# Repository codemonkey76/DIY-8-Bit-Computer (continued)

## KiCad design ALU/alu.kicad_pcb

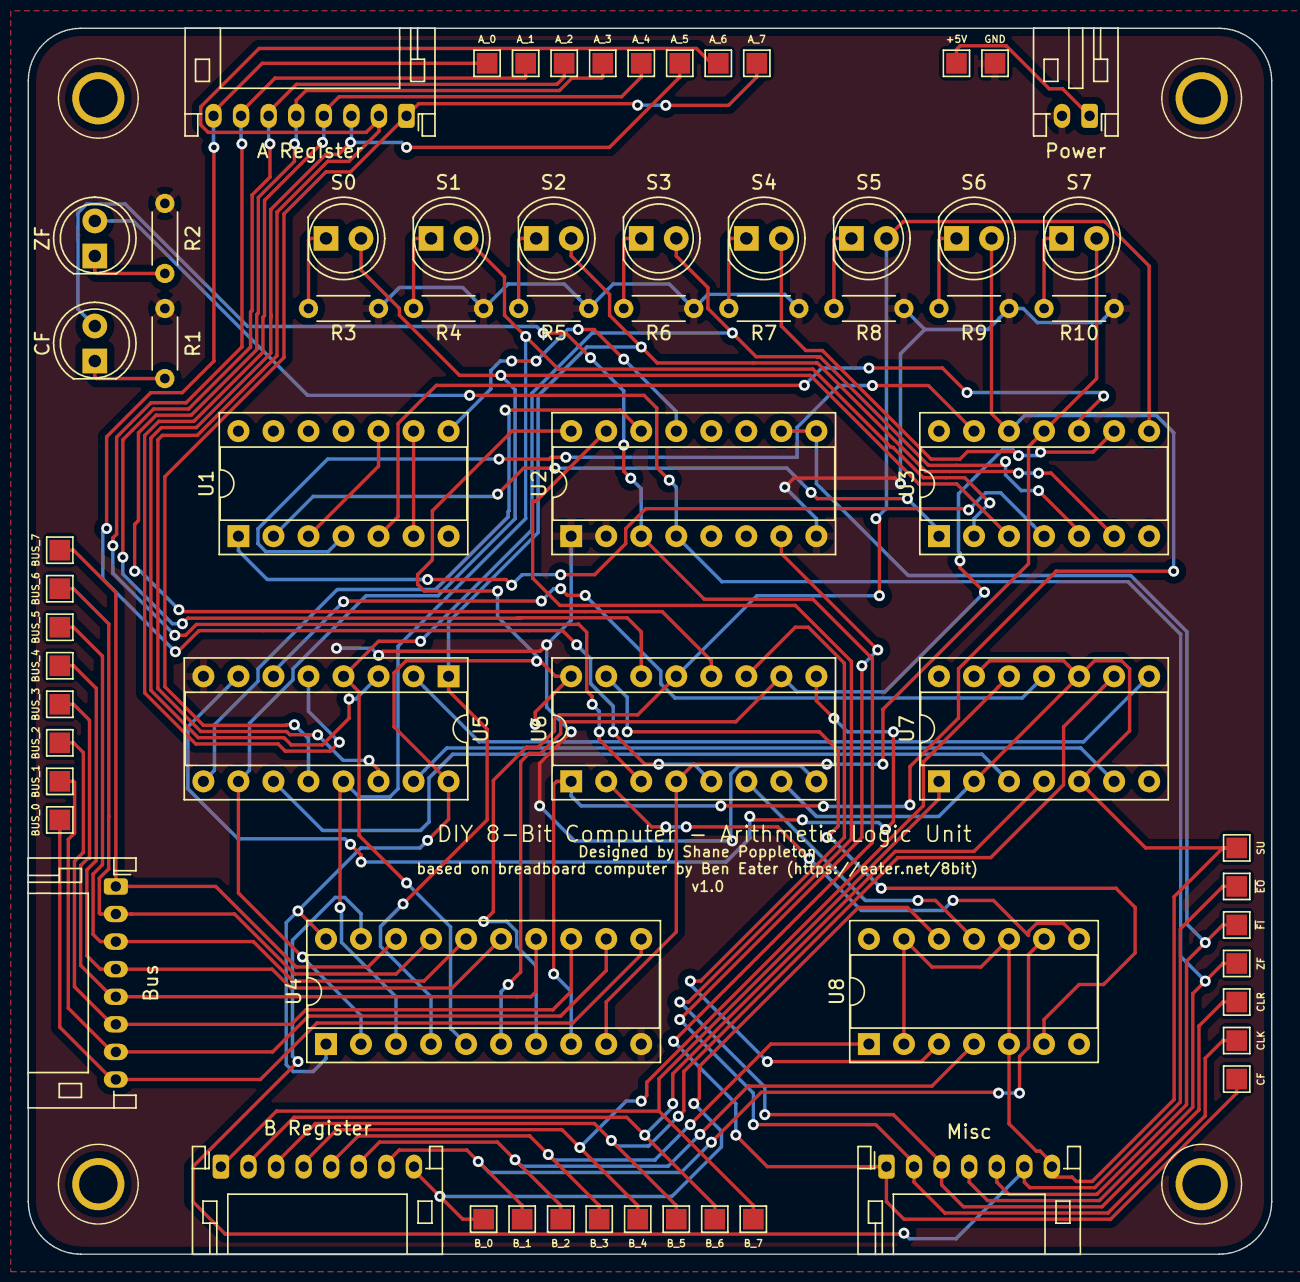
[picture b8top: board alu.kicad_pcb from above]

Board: 2 copper layers, 90.2 x 88.9 mm, 66 parts (0 on the bottom side), 68 nets.

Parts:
D1: CF; LED_D5.0mm
D2: ZF; LED_D5.0mm
D3: S0; LED_D5.0mm
D4: S1; LED_D5.0mm
D5: S2; LED_D5.0mm
D6: S3; LED_D5.0mm
D7: S4; LED_D5.0mm
D8: S5; LED_D5.0mm
D9: S6; LED_D5.0mm
D10: S7; LED_D5.0mm
J1: Bus; JST_PH_S8B-PH-K_1x08_P2.00mm_Horizontal
J2: Power; JST_PH_S2B-PH-K_1x02_P2.00mm_Horizontal
J3: Misc; JST_PH_S7B-PH-K_1x07_P2.00mm_Horizontal
J4: A Register; JST_PH_S8B-PH-K_1x08_P2.00mm_Horizontal
J5: B Register; JST_PH_S8B-PH-K_1x08_P2.00mm_Horizontal
R1, R2, R3, R4, R5, R6, R7, R8, R9, R10: 220R; R_Axial_DIN0204_L3.6mm_D1.6mm_P5.08mm_Horizontal
TP1: CF; TestPoint_Pad_1.5x1.5mm
TP2: ZF; TestPoint_Pad_1.5x1.5mm
TP3: ~FI~; TestPoint_Pad_1.5x1.5mm
TP4: CLK; TestPoint_Pad_1.5x1.5mm
TP5: CLR; TestPoint_Pad_1.5x1.5mm
TP6: BUS_0; TestPoint_Pad_1.5x1.5mm
TP7: BUS_1; TestPoint_Pad_1.5x1.5mm
TP8: BUS_2; TestPoint_Pad_1.5x1.5mm
TP9: BUS_3; TestPoint_Pad_1.5x1.5mm
TP10: BUS_4; TestPoint_Pad_1.5x1.5mm
TP11: BUS_5; TestPoint_Pad_1.5x1.5mm
TP12: BUS_6; TestPoint_Pad_1.5x1.5mm
TP13: BUS_7; TestPoint_Pad_1.5x1.5mm
TP14: +5V; TestPoint_Pad_1.5x1.5mm
TP15: GND; TestPoint_Pad_1.5x1.5mm
TP16: A_0; TestPoint_Pad_1.5x1.5mm
TP17: A_1; TestPoint_Pad_1.5x1.5mm
TP18: A_2; TestPoint_Pad_1.5x1.5mm
TP19: B_0; TestPoint_Pad_1.5x1.5mm
TP20: A_3; TestPoint_Pad_1.5x1.5mm
TP21: B_1; TestPoint_Pad_1.5x1.5mm
TP22: A_4; TestPoint_Pad_1.5x1.5mm
TP23: B_2; TestPoint_Pad_1.5x1.5mm
TP24: A_5; TestPoint_Pad_1.5x1.5mm
TP25: SU; TestPoint_Pad_1.5x1.5mm
TP26: B_3; TestPoint_Pad_1.5x1.5mm
TP27: A_6; TestPoint_Pad_1.5x1.5mm
TP28: B_4; TestPoint_Pad_1.5x1.5mm
TP29: A_7; TestPoint_Pad_1.5x1.5mm
TP30: B_5; TestPoint_Pad_1.5x1.5mm
TP31: B_6; TestPoint_Pad_1.5x1.5mm
TP32: B_7; TestPoint_Pad_1.5x1.5mm
TP33: ~EO~; TestPoint_Pad_1.5x1.5mm
U1: 74LS08; DIP-14_W7.62mm_Socket
U2: 74LS173; DIP-16_W7.62mm_Socket
U3: 74LS02; DIP-14_W7.62mm_Socket
U4: 74LS245; DIP-20_W7.62mm_Socket
U5, U6: 74LS283; DIP-16_W7.62mm_Socket
U7, U8: 74LS86; DIP-14_W7.62mm_Socket

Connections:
+5V: J2.1, TP14.1, U2.16, U4.1, U4.20, U5.16, U6.16
/A_0: J4.8, TP16.1, U6.5
/A_1: J4.7, TP17.1, U6.3
/A_2: J4.6, TP18.1, U6.14
/A_3: J4.5, TP20.1, U6.12
/A_4: J4.4, TP22.1, U5.5
/A_5: J4.3, TP24.1, U5.3
/A_6: J4.2, TP27.1, U5.14
/A_7: J4.1, TP29.1, U5.12
/BUS_0: J1.8, TP6.1, U4.11
/BUS_1: J1.7, TP7.1, U4.12
/BUS_2: J1.6, TP8.1, U4.13
/BUS_3: J1.5, TP9.1, U4.14
/BUS_4: J1.4, TP10.1, U4.15
/BUS_5: J1.3, TP11.1, U4.16
/BUS_6: J1.2, TP12.1, U4.17
/BUS_7: J1.1, TP13.1, U4.18
/B_0: J5.8, TP19.1, U8.12
/B_1: J5.7, TP21.1, U8.9
/B_2: J5.6, TP23.1, U8.4
/B_3: J5.5, TP26.1, U8.1
/B_4: J5.4, TP28.1, U7.12
/B_5: J5.3, TP30.1, U7.9
/B_6: J5.2, TP31.1, U7.4
/B_7: J5.1, TP32.1, U7.1
/SU: J3.7, TP25.1, U6.7, U7.2, U7.5, U7.10, U7.13, U8.2, U8.5, U8.10, U8.13
/~EO~: J3.6, TP33.1, U4.19
CF: D1.2, J3.1, TP1.1, U2.3
CLK: J3.2, TP4.1, U2.7
CLR: J3.3, TP5.1, U2.15
GND: J2.2, R1.1, R2.1, R3.2, R4.2, R5.2, R6.2, R7.2, R8.2, R9.2, R10.2, TP15.1, U2.1, U2.2, U2.8, U4.10, U5.8, U6.8
unnamed: D1.1, R1.2
unnamed: D2.1, R2.2
unnamed: D3.1, R3.1
unnamed: D3.2, U3.3, U4.2, U5.10
unnamed: D4.1, R4.1
unnamed: D4.2, U3.2, U4.3, U5.13
unnamed: D5.1, R5.1
unnamed: D5.2, U3.6, U4.4, U5.1
unnamed: D6.1, R6.1
unnamed: D6.2, U3.5, U4.5, U5.4
unnamed: D7.1, R7.1
unnamed: D7.2, U3.9, U4.6, U6.10
unnamed: D8.1, R8.1
unnamed: D8.2, U3.8, U4.7, U6.13
unnamed: D9.1, R9.1
unnamed: D9.2, U3.12, U4.8, U6.1
unnamed: D10.1, R10.1
unnamed: D10.2, U3.11, U4.9, U6.4
unnamed: U1.1, U3.4
unnamed: U1.2, U3.1
unnamed: U1.4, U3.13
unnamed: U1.5, U3.10
unnamed: U1.6, U1.9
unnamed: U1.8, U2.13
unnamed: U1.3, U1.10
unnamed: U2.14, U5.9
unnamed: U5.2, U7.8
unnamed: U5.6, U7.11
unnamed: U5.7, U6.9
unnamed: U5.11, U7.3
unnamed: U5.15, U7.6
unnamed: U6.2, U8.8
unnamed: U6.6, U8.11
unnamed: U6.11, U8.3
unnamed: U6.15, U8.6
ZF: D2.2, J3.4, TP2.1, U2.4
~FI~: J3.5, TP3.1, U2.9, U2.10

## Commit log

2019-08-25 Added 3D Renders
2019-08-25 Deleted unnecessary backup files
2019-08-25 Removed more unnecessary backup files
2019-08-25 Clock: Added attributions, re-plotted gerbers
2019-08-25 Added Attribution on each PCB, and regenerated gerbers
